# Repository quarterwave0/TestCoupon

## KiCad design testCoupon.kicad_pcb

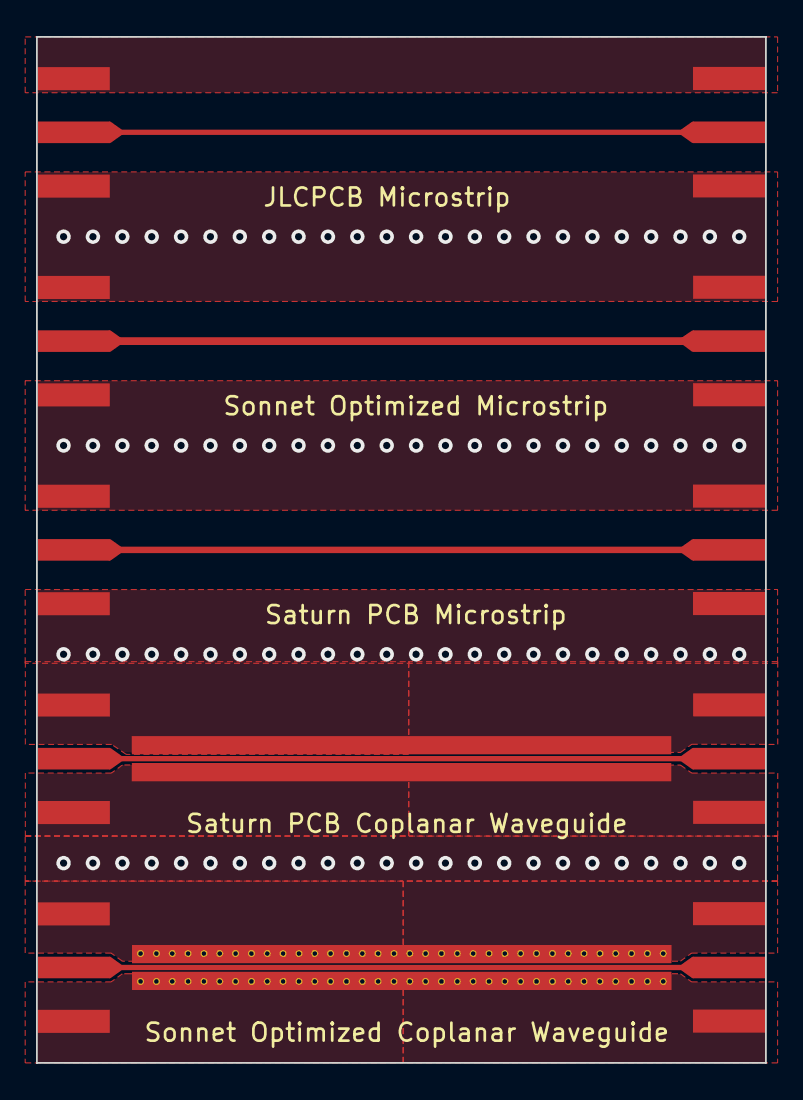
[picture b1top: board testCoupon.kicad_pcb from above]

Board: 4 copper layers, 40.5 x 57.0 mm, 12 parts (0 on the bottom side), 6 nets.

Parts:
J1, J2, J3, J4, J5, J6, J7, J8, J9, J10: Conn_Coaxial; ebaySMA
NT4: Saturn CPWG; SaturnCPWG
NT5: Sonnet CPWG; SonnetCPWG

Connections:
GND: J1.2 (Ext), J2.2 (Ext), J3.2 (Ext), J4.2 (Ext), J5.2 (Ext), J6.2 (Ext), J7.2 (Ext), J8.2 (Ext), J9.2 (Ext), J10.2 (Ext), NT4.2, NT5.2
unnamed: J1.1 (In), J2.1 (In)
unnamed: J3.1 (In), J4.1 (In)
unnamed: J5.1 (In), J6.1 (In)
unnamed: J7.1 (In), NT4.1
unnamed: J9.1 (In), NT5.1

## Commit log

2023-06-30 Spring cleaning
    guh?

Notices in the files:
testCoupon.kicad_pcb:
Made with <3 in San Diego - MIT Licence
